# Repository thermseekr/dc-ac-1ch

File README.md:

# DC-AC-1CH

Triac board with 1x 24 VDC input and 1x 220 AC output.

## LICENSE

This project is licensed under the [Creative Commons BY-NC 4.0 License](https://creativecommons.org/licenses/by-nc/4.0/).
Commercial use is not permitted without prior written consent. See the [LICENSE.txt](LICENSE.txt) file for details.

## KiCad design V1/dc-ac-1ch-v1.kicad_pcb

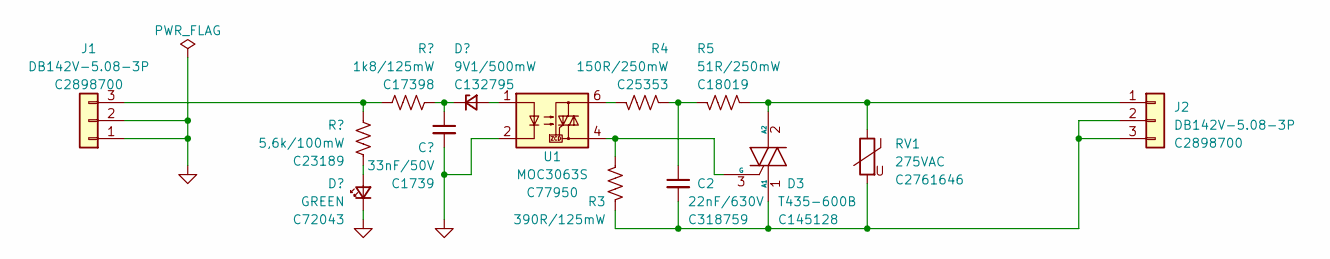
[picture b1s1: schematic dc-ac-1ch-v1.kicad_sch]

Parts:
C1: 33nF/50V; C_0805_2012Metric; LCSC Part # C1739
C2: 22nF/630V; C_1206_3216Metric; Mfr Part # CL31B223KHHNNNE; JLCPCB BOM 1
D1: GREEN; LED_0603_1608Metric; Mfr Part # 19-217/GHC-YR1S2/3T; LCSC Part # C72043
D2: 9V1/500mW; D_SOD-123; Mfr Part # MMSZ9V1T1G; JLCPCB BOM 1
D3: T435-600B; TO-252-2; Mfr Part # T435-600B-TR; JLCPCB BOM 1
J1, J2: DB142V-5.08-3P; TerminalBlock_Dibo_DB142V-5.08-3P_1x03_P5.08mm_Vertical; Mfr Part # DB142V-5.08-3P; JLCPCB BOM 1
R1: 5,6k/100mW; R_0603_1608Metric; Mfr Part # 0603WAF5601T5E; LCSC Part # C23189
R2: 1k8/125mW; R_0805_2012Metric; Mfr Part # 0805W8F1801T5E; LCSC Part # C17398
R3: 390R/125mW; R_0805_2012Metric; Mfr Part # 0805W8F3900T5E; JLCPCB BOM 1
R4: 150R/250mW; R_1206_3216Metric; Mfr Part # 1206W4J0151T5E; JLCPCB BOM 1
R5: 51R/250mW; R_1206_3216Metric; Mfr Part # 1206W4F510JT5E; JLCPCB BOM 1
RV1: 275VAC; RV_Disc_D9.50mm_W3.6mm_P5.08mm; Mfr Part # RM07D431KC1IE100; JLCPCB BOM 1
U1: MOC3063S; SMDIP-6_W9.53mm_Clearance8mm; Mfr Part # MOC3063S-TA1; JLCPCB BOM 1

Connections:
GND: C1.2, D1.1 (K), J1.1, J1.2, U1.2
unnamed: C2.1, R4.1, R5.2
unnamed: D1.2 (A), R1.2
unnamed: D2.2 (A), U1.1
unnamed: C1.1, D2.1 (K), R2.1
unnamed: C2.2, D3.1 (A1), J2.2, J2.3, R3.2, RV1.2
unnamed: D3.2 (A2), J2.1, R5.1, RV1.1
unnamed: D3.3 (G), R3.1, U1.4
unnamed: J1.3, R1.1, R2.2
unnamed: R4.2, U1.6

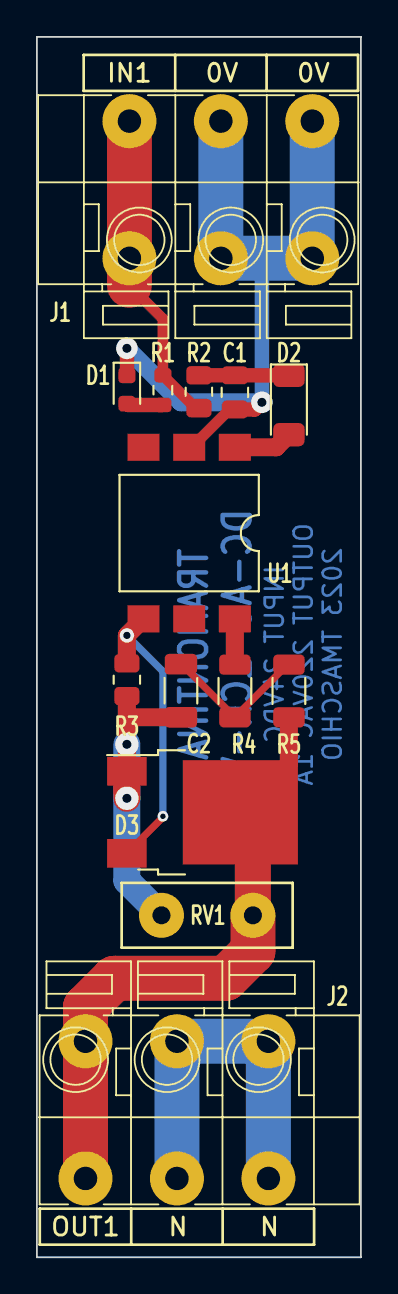
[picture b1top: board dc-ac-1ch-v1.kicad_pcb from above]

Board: 2 copper layers, 18.0 x 67.8 mm, 14 parts (0 on the bottom side), 10 nets.

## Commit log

2023-09-08 Repo cleanup
2023-09-08 Design completed.
2023-09-15 Final tweaks to production
2023-11-20 Silkscreen correction
2025-06-29 Added license
